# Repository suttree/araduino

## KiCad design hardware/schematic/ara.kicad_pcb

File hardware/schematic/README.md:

# Ara schematic, revision A prototype

This is the editable circuit for five or ten Arduino-compatible prototype boards. A routed `ara.kicad_pcb` and its `ara.kicad_pro` project now sit beside the schematic. The [quotation package](../manufacturing/rev-a/README.md) contains the board files, assembly files and firmware. Physical operation remains untested.

## Files

- `ara.kicad_sch`: self-contained KiCad 6-or-later schematic with embedded symbols and explicit physical pin numbers.
- `ara.svg`: zoomable review drawing of the same component and net definitions.
- `ara.net`: connectivity XML for review, generated by this project's script rather than by KiCad.
- `circuit.json`: component values, selected manufacturer part numbers, footprints and pin connections. The factory BOM is in `../manufacturing/rev-a/bom.csv`.
- `generate.py`: regenerates those four files using Python's standard library.
- `check.py`: reconstructs connections from the native schematic's symbols, wires and labels and checks the design requirements.
- `checks.json`: results of the most recent connectivity and calculation checks.
- `SOURCES.md`: datasheets, pin-map references and sourcing limitations.

Open `ara.kicad_pro` in KiCad to edit the schematic and PCB together. The drawing has six sections on a custom sheet that leaves the title block clear of components. Labels with the same name connect electrically even when there is no drawn wire between sections. The schematic-folder SVG is a separate rendering from the shared circuit model. The manufacturing package also includes KiCad's native SVG export, which was rendered and inspected.

## Circuit choices

The ATMEGA328P-AU is the surface-mount version of the processor in the working Uno. Its 32-pin package has different pin numbers from the existing 28-pin chip. The schematic uses TQFP pin 13, PB1/OC1A, for Arduino digital pin 9. VCC is 5 V and the three-pin resonator is 16 MHz. Both match the installed Arduino AVR Uno build configuration and the current `ara_birdsong` sketch. The CSTNE16M0V530000R0 resonator replaces the earlier CSTCE candidate and includes its 15 pF load capacitors. Murata publishes a comparison drawing for the two parts.

The USB-C receptacle has separate 5.1k pull-down resistors on CC1 and CC2. Both orientations' USB data contacts are connected to the CH340C USB-to-serial chip. The data lines have a USBLC6-2SC6 ESD protection array. A resettable fuse and TPS22918 load switch precede the board's power rail. The load switch slows the charging of the downstream capacitors. It is not a current regulator, a USB-PD controller or reverse-current protection.

The CH340C runs from 5 V. Its V3 pin has its own 100nF capacitor and is not tied to 5 V. Its TXD feeds the AVR's RXD through R4, and the AVR's TXD feeds the CH340C RXD through R5. A falling DTR edge resets the AVR through C10. D1 clamps the corresponding positive reset pulse. J2 provides conventional six-pin AVR ISP access for initial programming and recovery. U2 pin 8 is deliberately unused; it must not be treated as a crystal pin on CH340C.

The audio path takes the existing PWM output through two RC stages, a fixed attenuation network and a DC-blocking capacitor. The PAM8302A is an analogue-input amplifier, so it does not require a firmware port to I2S. The 100k/1k attenuation is a conservative starting point for quiet birdsong. It must be adjusted against a physical listening test. The linear calculation includes filter loading, the coupling capacitor, and a nominal 10k amplifier input resistance. It predicts about -18 dB net voltage gain from PWM baseband to the speaker at 1 kHz, including the amplifier's nominal gain of 15. That is a calculation, not a measured volume or power specification. The filter also attenuates the highest bird notes more than lower notes; compare all phrases before selecting final values.

The amplifier outputs are bridged. J3 connects between its two outputs through ferrite beads. Neither speaker lead connects to ground. C18/C19 provide high-frequency shunting after those beads. The speaker pair should be kept short and twisted, with enclosure strain relief.

R10/C17 provide a startup delay at the amplifier enable pin. Arduino digital pin 4 can pull the enable low through R11 if a later firmware change adds muting. The current sketch leaves that pin as an input, so the amplifier is enabled by the pull-up after the RC delay. The hardware delay does not wait for the bootloader to finish; startup/shutdown clicks and USB-reset clicks need testing. No firmware was changed for this draft.

## Power and programming

Use an external regulated 5 V USB supply for normal operation. An available 500mA-or-higher rating is a proposed supply choice, not the board's measured consumption or permission to draw that much from any USB host. The quiet attenuation is intended to keep demand modest. Measure startup, idle and audio current before release, including comparison with the CH340C's USB descriptors and the host's allowed current. USB suspend behaviour also needs review. An Rd resistor does not by itself authorize 1.5 A or 3 A of draw.

For the first prototypes, power the target through USB when using J2 and disable the programmer's target-power output. J2 pin 2 is a 5 V reference connection, not a second independent power input. This draft does not provide power-source arbitration.

Blank ATmega chips need initial ISP programming. The installed Arduino AVR 1.8.6 Uno configuration uses Optiboot, a 16 MHz clock, 115200-baud serial uploads and fuse bytes low `0xFF`, high `0xDE`, extended `0xFD`. Use the toolchain's documented bootloader-burning procedure and verify the exact purchased chip before setting fuses. Clock or fuse mistakes can prevent normal uploads. The factory must not substitute ATmega328PB or an unverified compatible device without a separate firmware and pinout review.

## Checks completed

Regenerate and check with:

```sh
python3 hardware/schematic/generate.py
python3 hardware/schematic/check.py
```

The checker reconstructs pin connections from the actual `.kicad_sch` geometry, verifies the independent `.net` agrees, checks USB orientation and CC wiring, AVR pin assignments, UART direction, reset diode polarity, recovery header order, supply connections, filter topology and isolated speaker outputs. Every pin has a connection or an intentional no-connect marker. KiUtils 1.4.8 also parsed the native schematic and round-tripped it successfully during authoring. The SVG was rendered and visually inspected with CairoSVG.

KiCad 10.0.8 was run from a verified official disk image on 25 November 2026. Native ERC reports zero findings. Native PCB DRC reports zero findings, zero unconnected items and zero schematic parity issues. The [reports](../manufacturing/rev-a/checks/) are retained with the manufacturing files. Native SVGs of the schematic and board were rendered and inspected. No circuit simulation or physical measurement has run.

Exact procurement parts are recorded in `../pcb/parts.json` and a dated public JLCPCB snapshot in `../pcb/sourcing.json`. The selected capacitors now use stocked X7R parts for small values and X5R parts for bulk supply capacitance. Their actual voltage ratings are recorded in the circuit. The ideal filter calculation does not model tolerance, DC bias or temperature. The ferrite beads are BLM21PG221SZ1D. The Alps SKRPACE010 reset switch has a custom footprint derived from its manufacturer's land pattern and contact diagram.

## Prototype quotation and ordering

1. Match all 27 part numbers in the factory quotation and inspect the corrected placement preview. Supplier rotation/origin corrections are retained separately from the KiCad layout. The dated stock snapshot is not a reservation. Do not substitute ATmega328PB for ATmega328P.
2. Include through-hole soldering for the speaker connector and programming header. Specify initial bootloader, fuse and firmware programming separately. Blank chips cannot accept USB serial uploads until their initial programming is complete.
3. Compare the five- and ten-board delivered prices. An independent review is an optional risk-reduction step before buying the prototype batch, as agreed with the owner.
4. Test the amplifier with the actual speaker after delivery. Compare quiet volume, high notes, silence and startup clicks with the working Uno. Supply current, USB behaviour and physical audio performance remain unverified.
5. Build the enclosure around the board and speaker. The board is 65 × 45 × 1.6 mm, excluding components and connector access. Four 3.2 mm mounting holes have 6.4 mm copper-free screw-head areas. The STEP file is the bare board, not an assembled clearance model.

The final speaker cable must arrive pre-fitted with the mating JST-PH plug. The owner should not need to solder or crimp it. Fit and retention remain physical tests for the assembled enclosure.

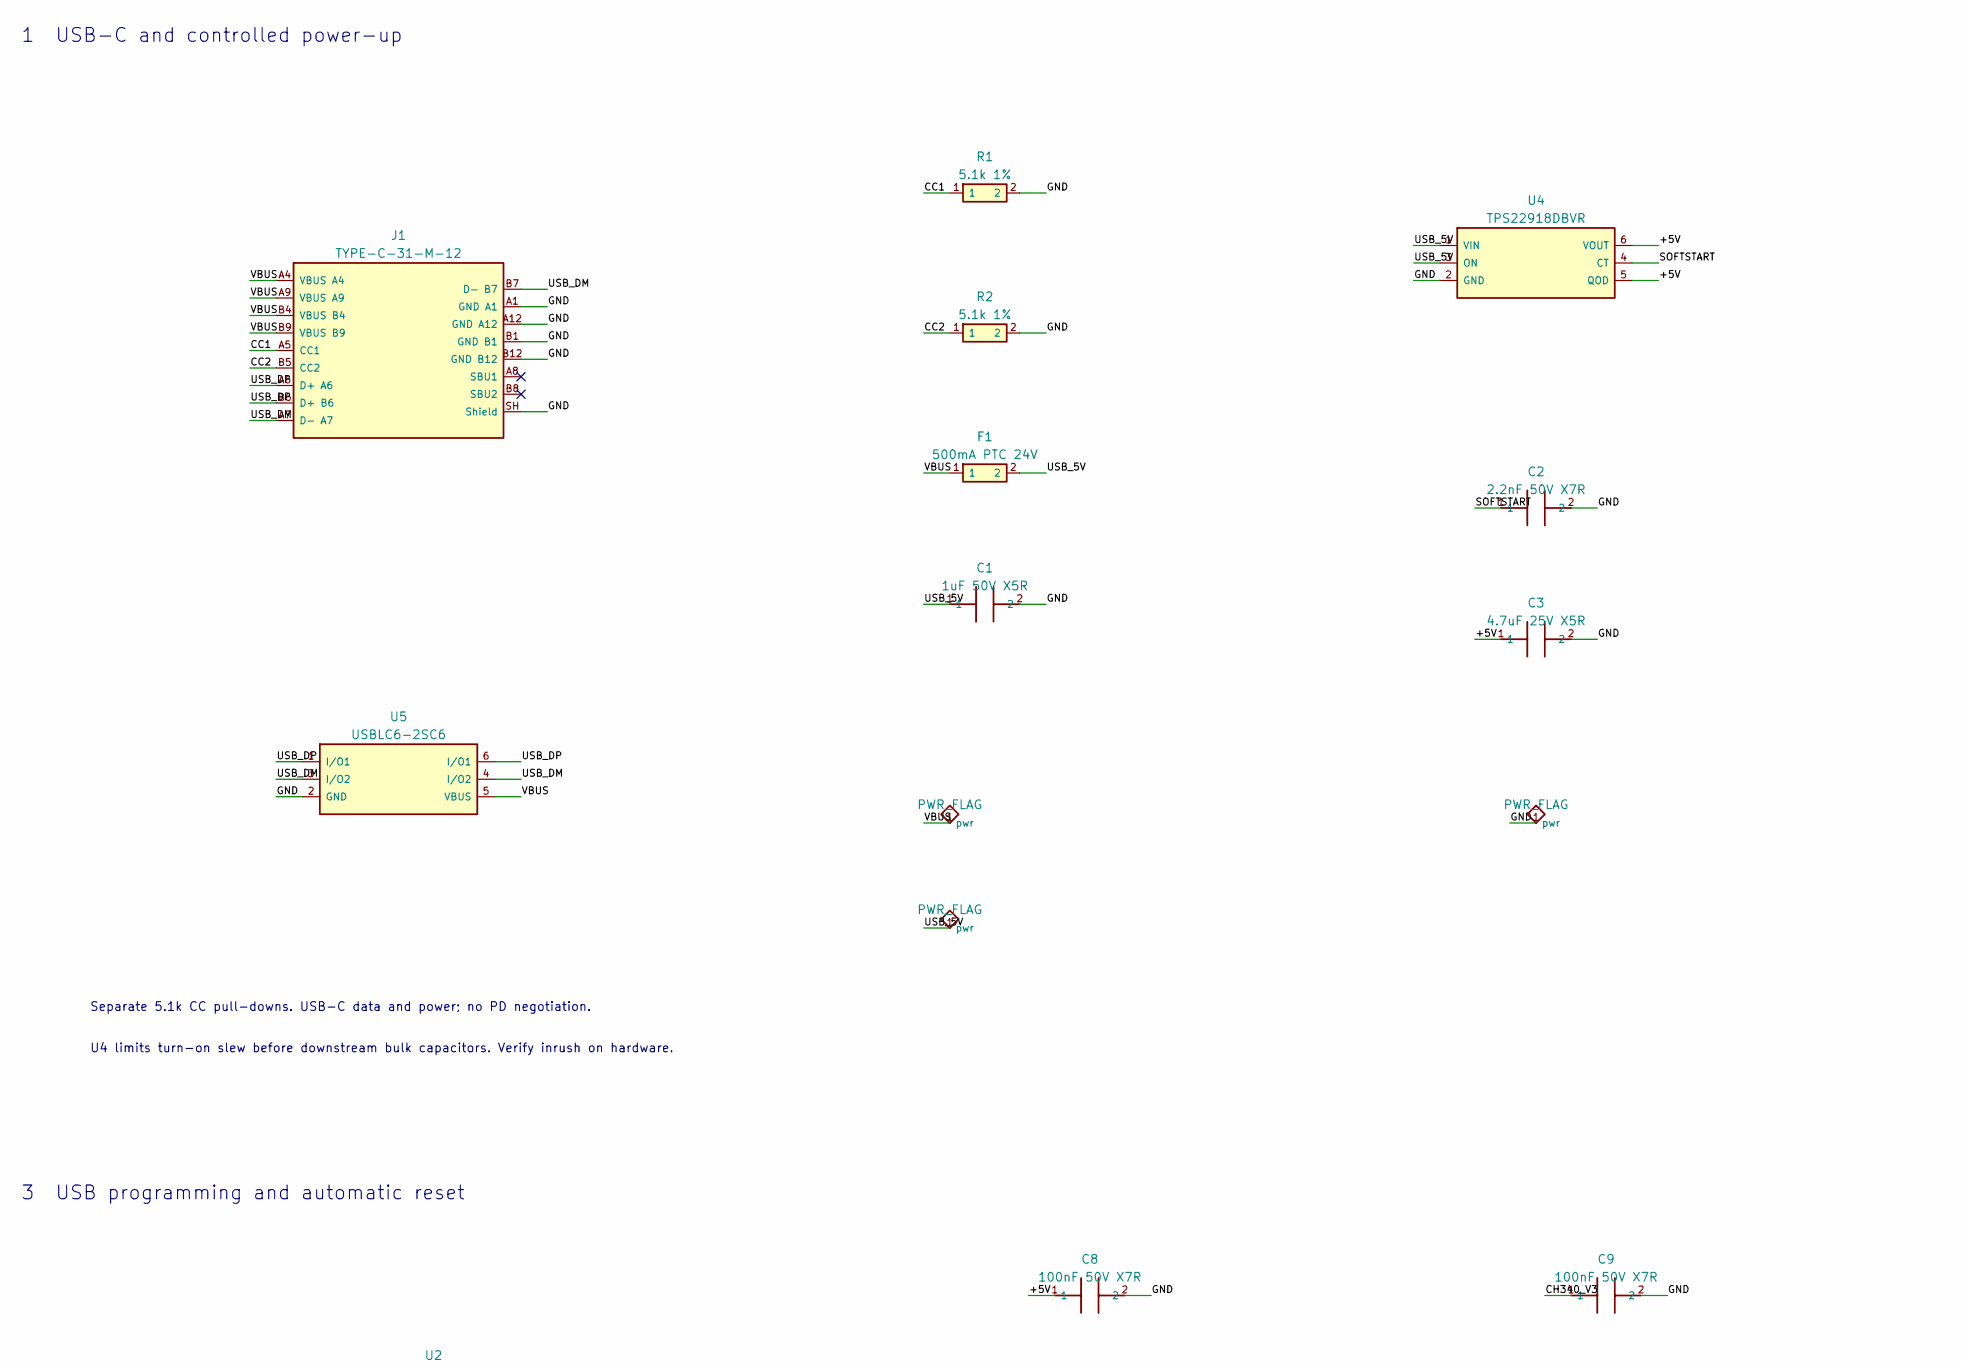
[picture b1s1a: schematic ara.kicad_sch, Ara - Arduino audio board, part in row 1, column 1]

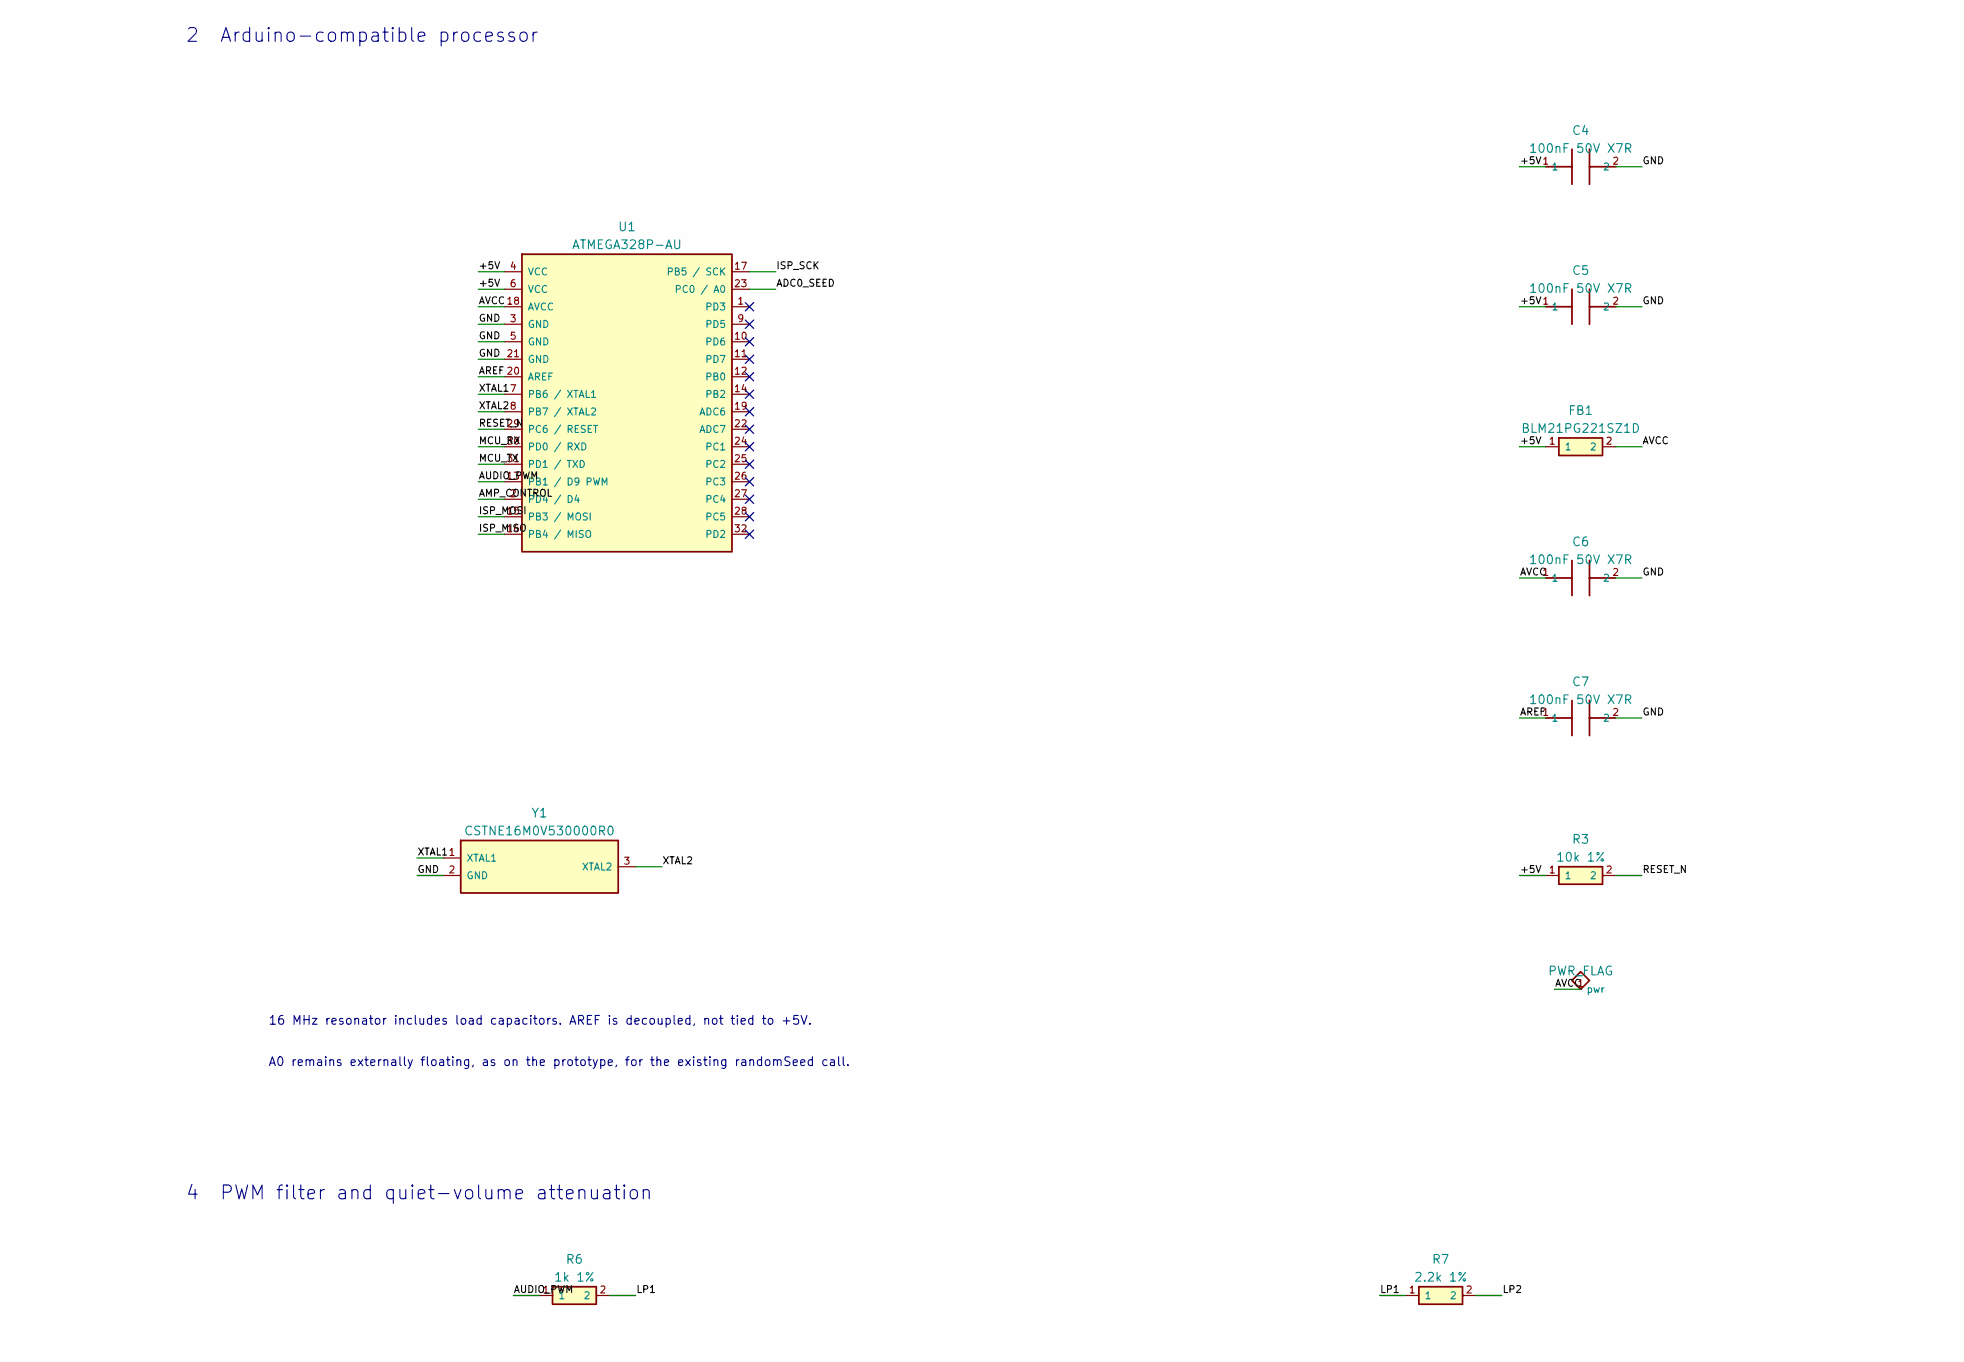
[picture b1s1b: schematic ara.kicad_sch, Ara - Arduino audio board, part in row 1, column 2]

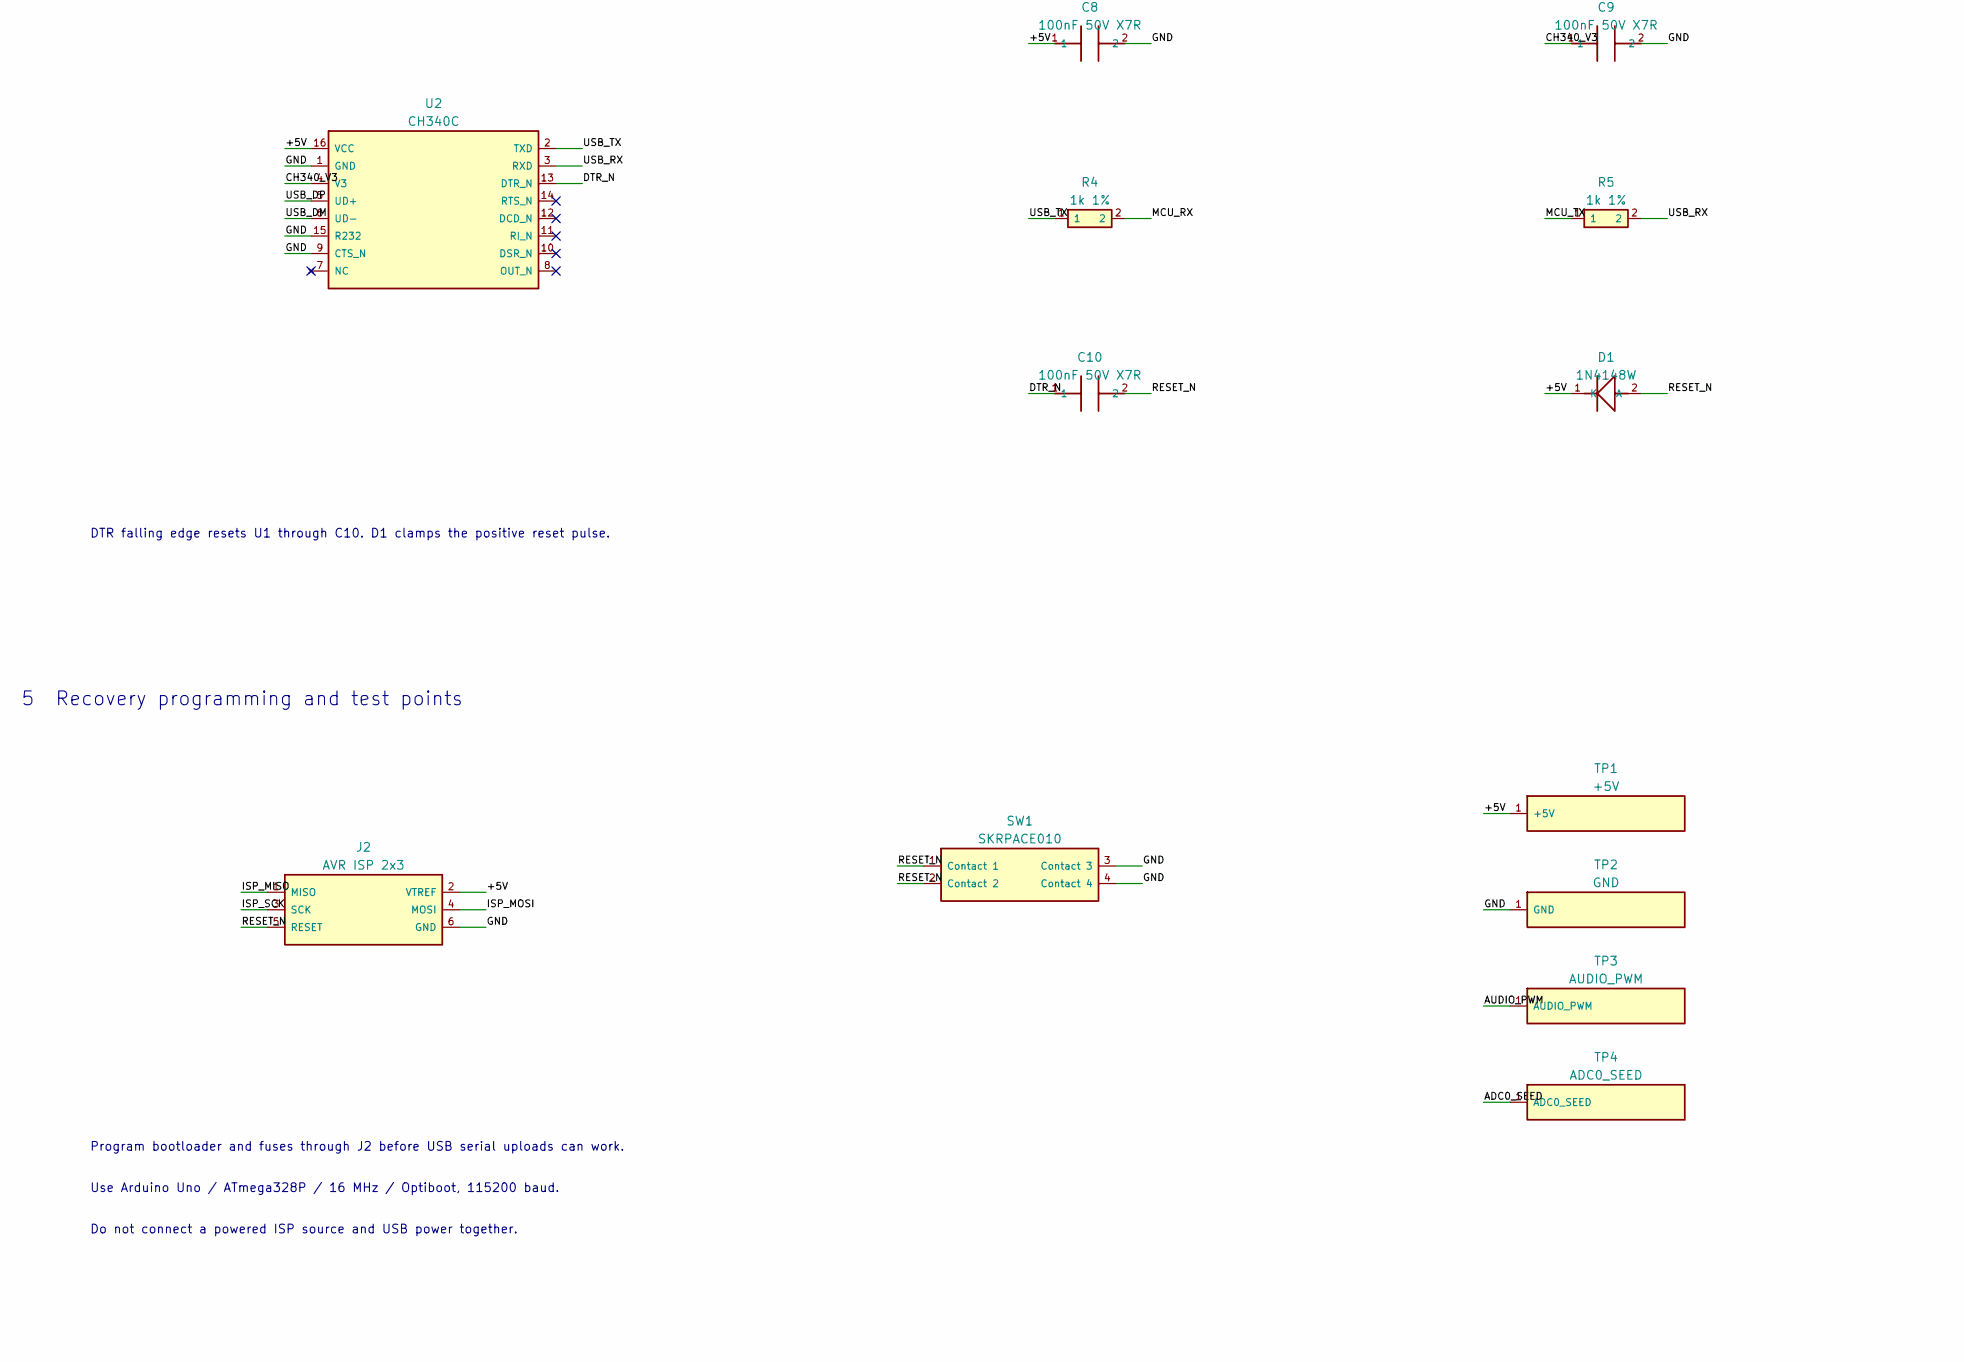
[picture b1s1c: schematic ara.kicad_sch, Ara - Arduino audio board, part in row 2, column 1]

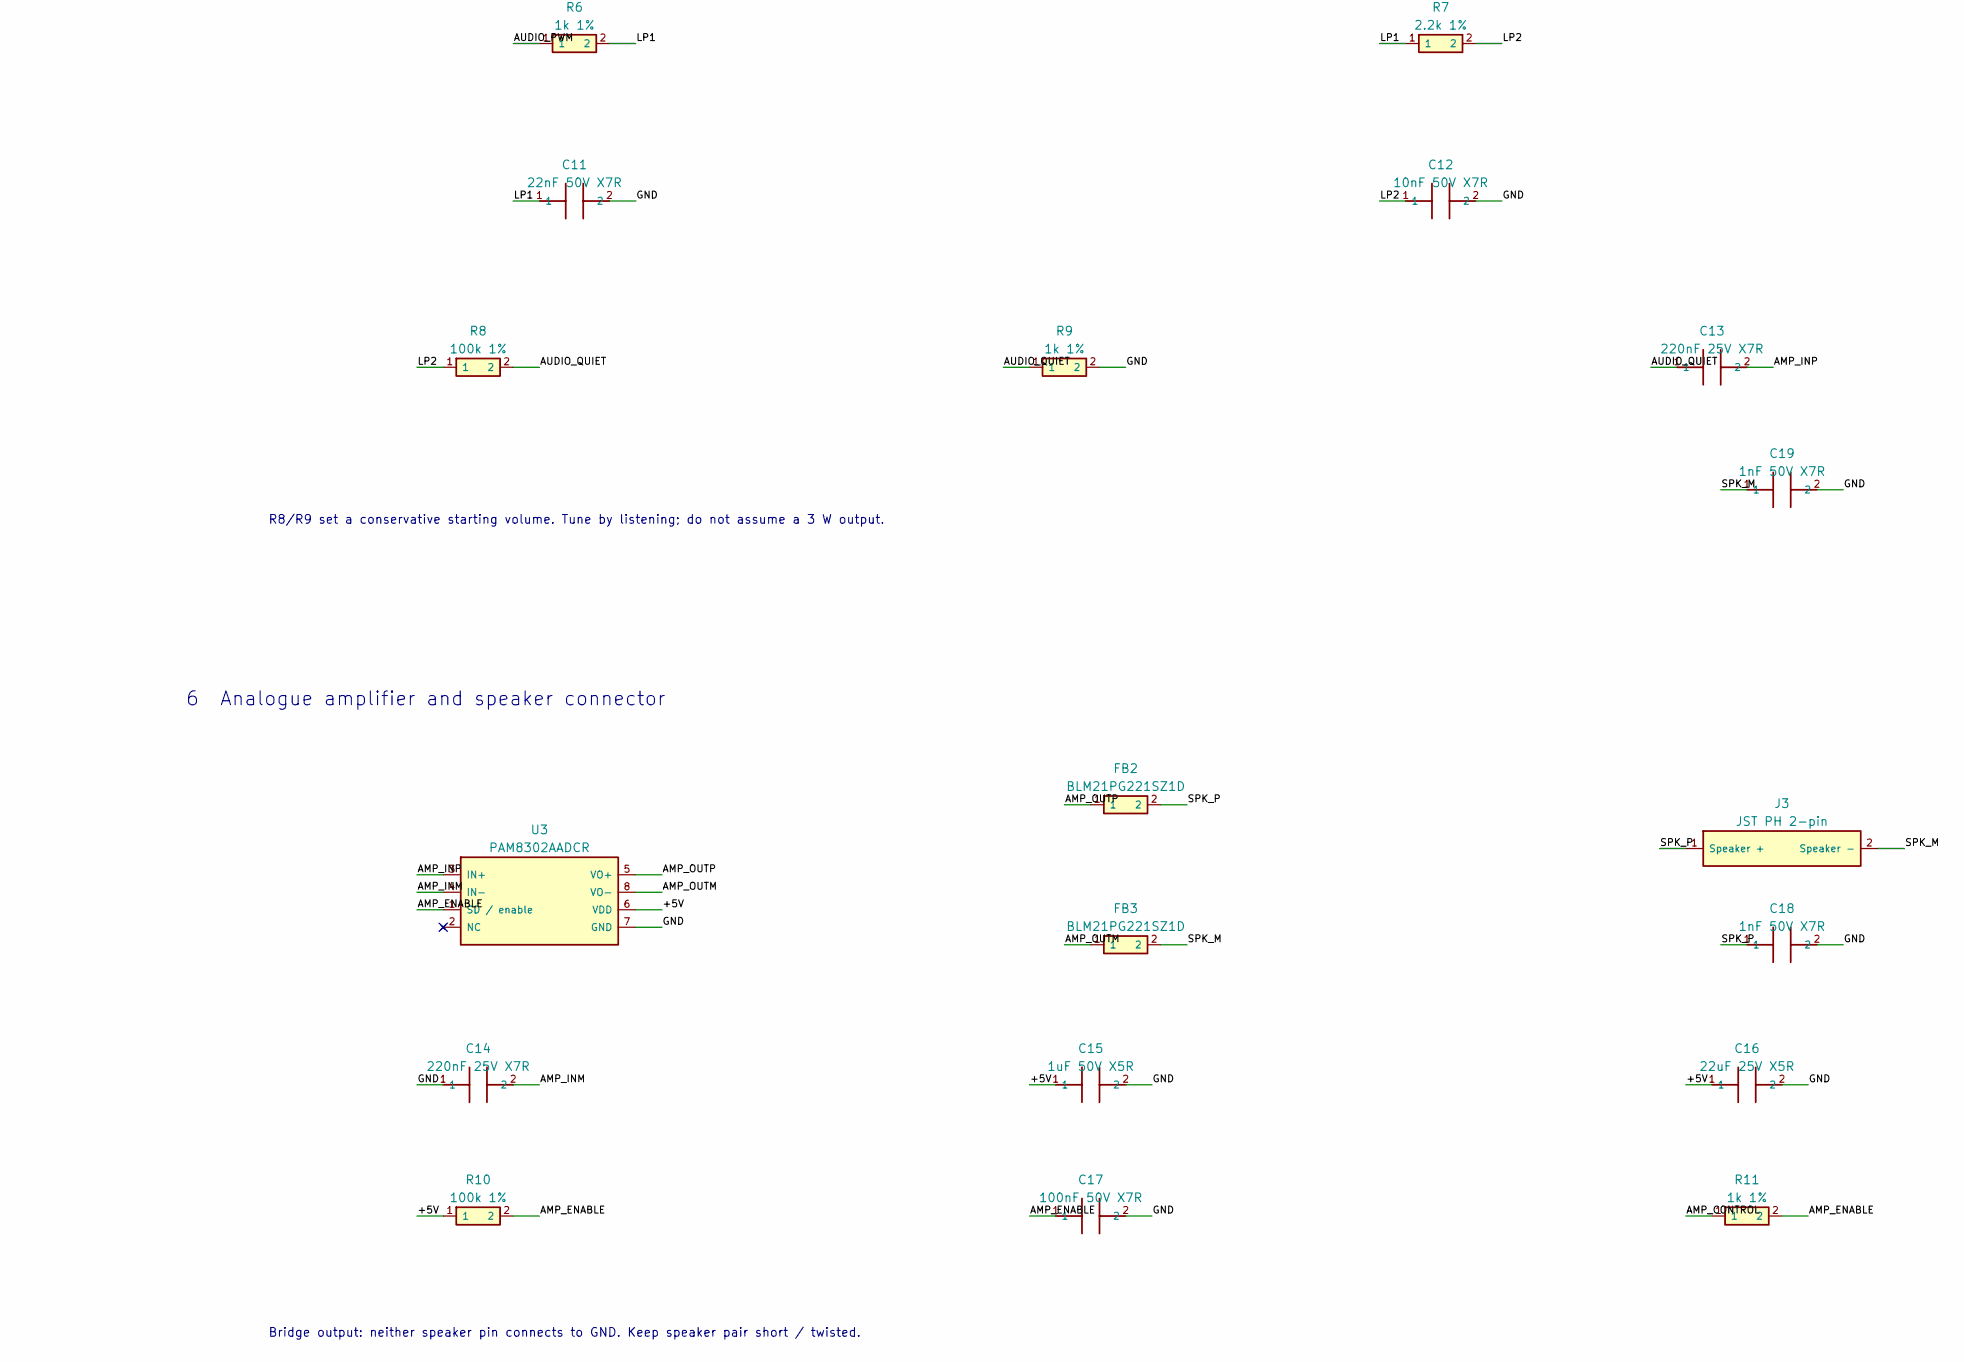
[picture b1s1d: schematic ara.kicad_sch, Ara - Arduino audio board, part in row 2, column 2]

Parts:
C1, C15: 1uF 50V X5R; C_0603_1608Metric; MPN CL10A105KB8NNNC; LCSC C15849
C2: 2.2nF 50V X7R; C_0603_1608Metric; MPN 0603B222K500NT; LCSC C1604
C3: 4.7uF 25V X5R; C_0805_2012Metric; MPN CL21A475KAQNNNE; LCSC C1779
C4, C5, C6, C7, C8, C9, C10, C17: 100nF 50V X7R; C_0603_1608Metric; MPN CC0603KRX7R9BB104; LCSC C14663
C11: 22nF 50V X7R; C_0603_1608Metric; MPN CL10B223KB8NNNC; LCSC C21122
C12: 10nF 50V X7R; C_0603_1608Metric; MPN 0603B103K500NT; LCSC C57112
C13, C14: 220nF 25V X7R; C_0603_1608Metric; MPN CL10B224KA8NNNC; LCSC C21120
C16: 22uF 25V X5R; C_1206_3216Metric; MPN CL31A226KAHNNNE; LCSC C12891
C18, C19: 1nF 50V X7R; C_0603_1608Metric; MPN CL10B102KB8NNNC; LCSC C1588
D1: 1N4148W; D_SOD-123; MPN 1N4148W; LCSC C2099
F1: 500mA PTC 24V; Fuse_1206_3216Metric; MPN nSMD050-24V; LCSC C70076
FB1, FB2, FB3: BLM21PG221SZ1D; L_0805_2012Metric; MPN BLM21PG221SZ1D; LCSC C437411
J1: TYPE-C-31-M-12; USB_C_Receptacle_HRO_TYPE-C-31-M-12; MPN TYPE-C-31-M-12; LCSC C165948
J2: AVR ISP 2x3; PinHeader_2x03_P2.54mm_Vertical; MPN FG-PZ2.54-02-03P; LCSC C42391443
J3: JST PH 2-pin; JST_PH_S2B-PH-K_1x02_P2.00mm_Horizontal; MPN S2B-PH-K-S(LF)(SN); LCSC C173752
R1, R2: 5.1k 1%; R_0603_1608Metric; MPN 0603WAF5101T5E; LCSC C23186
R3: 10k 1%; R_0603_1608Metric; MPN 0603WAF1002T5E; LCSC C25804
R4, R5, R6, R9, R11: 1k 1%; R_0603_1608Metric; MPN 0603WAF1001T5E; LCSC C21190
R7: 2.2k 1%; R_0603_1608Metric; MPN 0603WAF2201T5E; LCSC C4190
R8, R10: 100k 1%; R_0603_1608Metric; MPN 0603WAF1003T5E; LCSC C25803
SW1: SKRPACE010; SW_SKRPACE010; MPN SKRPACE010; LCSC C139797
TP1: +5V; TestPoint_Pad_D1.5mm
TP2: GND; TestPoint_Pad_D1.5mm
TP3: AUDIO_PWM; TestPoint_Pad_D1.5mm
TP4: ADC0_SEED; TestPoint_Pad_D1.5mm
U1: ATMEGA328P-AU; TQFP-32_7x7mm_P0.8mm; MPN ATMEGA328P-AU; LCSC C14877
U2: CH340C; SOIC-16_3.9x9.9mm_P1.27mm; MPN CH340C; LCSC C84681
U3: PAM8302AADCR; SOIC-8_3.9x4.9mm_P1.27mm; MPN PAM8302AADCR; LCSC C112137
U4: TPS22918DBVR; SOT-23-6; MPN TPS22918DBVR; LCSC C131941
U5: USBLC6-2SC6; SOT-23-6; MPN USBLC6-2SC6; LCSC C7519
Y1: CSTNE16M0V530000R0; Resonator_SMD_Murata_CSTxExxV-3Pin_3.0x1.1mm; MPN CSTNE16M0V530000R0; LCSC C341521

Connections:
/+5V: C3.1, C4.1, C5.1, C8.1, C15.1, C16.1, D1.1 (K), FB1.1, J2.2 (VTREF), R3.1, R10.1, TP1.1, U1.4 (VCC), U1.6 (VCC), U2.16 (VCC), U3.6 (VDD), U4.5 (QOD), U4.6 (VOUT)
/ADC0_SEED: TP4.1, U1.23 (PC0 / A0)
/AMP_CONTROL: R11.1, U1.2 (PD4 / D4)
/AMP_ENABLE: C17.1, R10.2, R11.2, U3.1 (SD / enable)
/AMP_INM: C14.2, U3.4 (IN-)
/AMP_INP: C13.2, U3.3 (IN+)
/AMP_OUTM: FB3.1, U3.8 (VO-)
/AMP_OUTP: FB2.1, U3.5 (VO+)
/AREF: C7.1, U1.20 (AREF)
/AUDIO_PWM: R6.1, TP3.1, U1.13 (PB1 / D9 PWM)
/AUDIO_QUIET: C13.1, R8.2, R9.1
/AVCC: C6.1, FB1.2, U1.18 (AVCC)
/CC1: J1.A5 (CC1), R1.1
/CC2: J1.B5 (CC2), R2.1
/CH340_V3: C9.1, U2.4 (V3)
/DTR_N: C10.1, U2.13 (DTR_N)
/GND: C1.2, C2.2, C3.2, C4.2, C5.2, C6.2, C7.2, C8.2, C9.2, C11.2, C12.2, C14.1, C15.2, C16.2, C17.2, C18.2, C19.2, J1.A1 (GND A1), J1.A12 (GND A12), J1.B1 (GND B1), J1.B12 (GND B12), J1.SH (Shield), J2.6 (GND), R1.2, R2.2, R9.2, SW1.3 (Contact 3), SW1.4 (Contact 4), TP2.1, U1.3 (GND), U1.5 (GND), U1.21 (GND), U2.1 (GND), U2.9 (CTS_N), U2.15 (R232), U3.7 (GND), U4.2 (GND), U5.2 (GND), Y1.2 (GND)
/ISP_MISO: J2.1 (MISO), U1.16 (PB4 / MISO)
/ISP_MOSI: J2.4 (MOSI), U1.15 (PB3 / MOSI)
/ISP_SCK: J2.3 (SCK), U1.17 (PB5 / SCK)
/LP1: C11.1, R6.2, R7.1
/LP2: C12.1, R7.2, R8.1
/MCU_RX: R4.2, U1.30 (PD0 / RXD)
/MCU_TX: R5.1, U1.31 (PD1 / TXD)
/RESET_N: C10.2, D1.2 (A), J2.5 (RESET), R3.2, SW1.1 (Contact 1), SW1.2 (Contact 2), U1.29 (PC6 / RESET)
/SOFTSTART: C2.1, U4.4 (CT)
/SPK_M: C19.1, FB3.2, J3.2 (Speaker -)
/SPK_P: C18.1, FB2.2, J3.1 (Speaker +)
/USB_5V: C1.1, F1.2, U4.1 (VIN), U4.3 (ON)
/USB_DM: J1.A7 (D- A7), J1.B7 (D- B7), U2.6 (UD-), U5.3 (I/O2), U5.4 (I/O2)
/USB_DP: J1.A6 (D+ A6), J1.B6 (D+ B6), U2.5 (UD+), U5.1 (I/O1), U5.6 (I/O1)
/USB_RX: R5.2, U2.3 (RXD)
/USB_TX: R4.1, U2.2 (TXD)
/VBUS: F1.1, J1.A4 (VBUS A4), J1.A9 (VBUS A9), J1.B4 (VBUS B4), J1.B9 (VBUS B9), U5.5 (VBUS)
/XTAL1: U1.7 (PB6 / XTAL1), Y1.1 (XTAL1)
/XTAL2: U1.8 (PB7 / XTAL2), Y1.3 (XTAL2)

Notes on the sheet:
1 USB-C and controlled power-up
2 Arduino-compatible processor
3 USB programming and automatic reset
4 PWM filter and quiet-volume attenuation
5 Recovery programming and test points
6 Analogue amplifier and speaker connector
Separate 5.1k CC pull-downs. USB-C data and power; no PD negotiation.
U4 limits turn-on slew before downstream bulk capacitors. Verify inrush on hardware.
16 MHz resonator includes load capacitors. AREF is decoupled, not tied to +5V.
A0 remains externally floating, as on the prototype, for the existing randomSeed call.
DTR falling edge resets U1 through C10. D1 clamps the positive reset pulse.
R8/R9 set a conservative starting volume. Tune by listening; do not assume a 3 W output.
Program bootloader and fuses through J2 before USB serial uploads can work.
Use Arduino Uno / ATmega328P / 16 MHz / Optiboot, 115200 baud.
Do not connect a powered ISP source and USB power together.
Bridge output: neither speaker pin connects to GND. Keep speaker pair short / twisted.

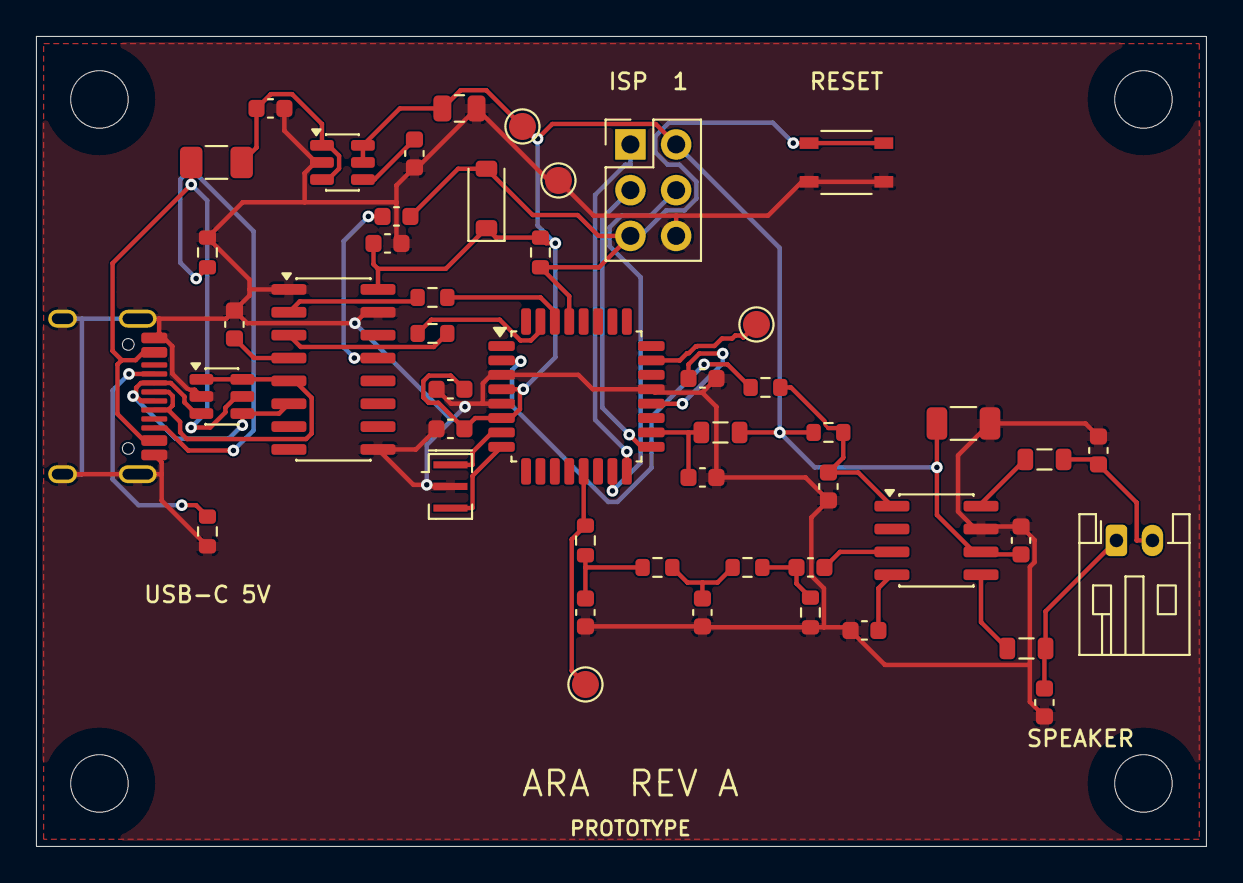
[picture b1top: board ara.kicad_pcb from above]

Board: 2 copper layers, 65.0 x 45.0 mm, 53 parts (0 on the bottom side), 36 nets.

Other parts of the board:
H1, H2, H3, H4: MountingHole_3.2mm_M3

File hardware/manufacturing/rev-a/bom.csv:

Comment,Designator,Footprint,LCSC Part #
ATMEGA328P-AU,U1,Package_QFP:TQFP-32_7x7mm_P0.8mm,C14877
CH340C,U2,Package_SO:SOIC-16_3.9x9.9mm_P1.27mm,C84681
PAM8302AADCR,U3,Package_SO:SOIC-8_3.9x4.9mm_P1.27mm,C112137
TPS22918DBVR,U4,Package_TO_SOT_SMD:SOT-23-6,C131941
USBLC6-2SC6,U5,Package_TO_SOT_SMD:SOT-23-6,C7519
TYPE-C-31-M-12,J1,Connector_USB:USB_C_Receptacle_HRO_TYPE-C-31-M-12,C165948
AVR ISP 2x3,J2,Connector_PinHeader_2.54mm:PinHeader_2x03_P2.54mm_Vertical,C42391443
JST PH 2-pin,J3,Connector_JST:JST_PH_S2B-PH-K_1x02_P2.00mm_Horizontal,C173752
CSTNE16M0V530000R0,Y1,Crystal:Resonator_SMD_Murata_CSTxExxV-3Pin_3.0x1.1mm,C341521
BLM21PG221SZ1D,"FB1,FB2,FB3",Inductor_SMD:L_0805_2012Metric,C437411
SKRPACE010,SW1,AraBoard:SW_SKRPACE010,C139797
500mA PTC 24V,F1,Fuse:Fuse_1206_3216Metric,C70076
1N4148W,D1,Diode_SMD:D_SOD-123,C2099
1k 1%,"R4,R5,R6,R9,R11",Resistor_SMD:R_0603_1608Metric,C21190
5.1k 1%,"R1,R2",Resistor_SMD:R_0603_1608Metric,C23186
10k 1%,R3,Resistor_SMD:R_0603_1608Metric,C25804
2.2k 1%,R7,Resistor_SMD:R_0603_1608Metric,C4190
100k 1%,"R8,R10",Resistor_SMD:R_0603_1608Metric,C25803
100nF 50V X7R,"C4,C5,C6,C7,C8,C9,C10,C17",Capacitor_SMD:C_0603_1608Metric,C14663
1uF 50V X5R,"C1,C15",Capacitor_SMD:C_0603_1608Metric,C15849
4.7uF 25V X5R,C3,Capacitor_SMD:C_0805_2012Metric,C1779
22uF 25V X5R,C16,Capacitor_SMD:C_1206_3216Metric,C12891
220nF 25V X7R,"C13,C14",Capacitor_SMD:C_0603_1608Metric,C21120
2.2nF 50V X7R,C2,Capacitor_SMD:C_0603_1608Metric,C1604
22nF 50V X7R,C11,Capacitor_SMD:C_0603_1608Metric,C21122
10nF 50V X7R,C12,Capacitor_SMD:C_0603_1608Metric,C57112
1nF 50V X7R,"C18,C19",Capacitor_SMD:C_0603_1608Metric,C1588

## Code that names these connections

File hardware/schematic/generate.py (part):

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    (4,'VCC','power_in','+5V'), (6,'VCC','power_in','+5V'),
    (18,'AVCC','power_in','AVCC'), (3,'GND','power_in','GND'),
    (5,'GND','power_in','GND'), (21,'GND','power_in','GND'),
    (20,'AREF','passive','AREF'), (7,'PB6 / XTAL1','input','XTAL1'),
    (8,'PB7 / XTAL2','output','XTAL2'), (29,'PC6 / RESET','input','RESET_N'),
    (30,'PD0 / RXD','input','MCU_RX'), (31,'PD1 / TXD','output','MCU_TX'),
    (13,'PB1 / D9 PWM','output','AUDIO_PWM'), (2,'PD4 / D4','bidirectional','AMP_CONTROL'),
    (15,'PB3 / MOSI','bidirectional','ISP_MOSI'), (16,'PB4 / MISO','bidirectional','ISP_MISO'),
    (17,'PB5 / SCK','bidirectional','ISP_SCK'), (23,'PC0 / A0','input','ADC0_SEED'),
    (1,'PD3','bidirectional',None), (9,'PD5','bidirectional',None),
    (10,'PD6','bidirectional',None), (11,'PD7','bidirectional',None),
    (12,'PB0','bidirectional',None), (14,'PB2','bidirectional',None),
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
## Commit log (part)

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2024-12-25 tidy up basic working code
2024-12-25 tweak a few melodies
2024-12-25 project icons
2024-12-27 tidy
2024-12-28 sing more frequently at sunrise and sunset
2025-01-04 added a melody
2025-01-10 within 10 minutes of sunrise
2025-03-02 commented out date setter
2025-03-02 libs
